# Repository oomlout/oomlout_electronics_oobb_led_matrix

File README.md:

# oomlout_oobb_led_matrix
## Description
an electronics project that is an led matrix in the oobb shape, current version is 3 x 10 oobb with 6 columns and 15 rows of leds, it uses the aip1640 16 x 8 driver chip/

## Images

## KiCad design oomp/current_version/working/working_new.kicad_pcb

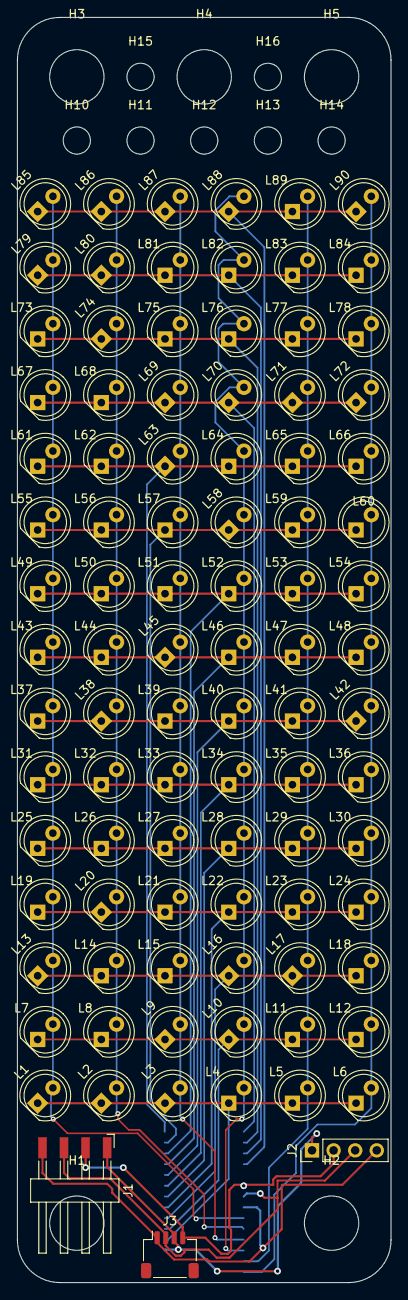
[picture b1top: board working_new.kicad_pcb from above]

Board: 2 copper layers, 44.0 x 149.0 mm, 106 parts (1 on the bottom side), 25 nets.

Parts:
H1, H2, H3, H4, H5: mhm6_fbea65_electronic_mounting_hole_m6
H10, H11, H12, H13, H14, H15, H16: mhm3_872f01_electronic_mounting_hole_m3
J1: hi14psmra_70c043_electronic_header_2d54_mm_4_pin_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; hi14psmra_70c043_electronic_header_2d54_mm_4_pin_surface_mo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
J2: hi14p_abf4a4_electronic_header_2d54_mm_4_pin
J3: h4psmra_adfe77_electronic_header_1_mm_jst_sh_4_pi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; h4psmra_adfe77_electronic_header_1_mm_jst_sh_4_pin_surface_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
L1, L2, L3, L4, L5, L6, L7, L8, L9, L10, L11, L12, L13, L14, L15, L16, L17, L18, L19, L20, L21, L22, L23, L24, L25, L26, L27, L28, L29, L30, L31, L32, L33, L34, L35, L36, L37, L38, L39, L40, L41, L42, L43, L44, L45, L46, L47, L48, L49, L50, L51, L52, L53, L54, L55, L56, L57, L58, L59, L60, L61, L62, L63, L64, L65, L66, L67, L68, L69, L70, L71, L72, L73, L74, L75, L76, L77, L78, L79, L80, L81, L82, L83, L84, L85, L86, L87, L88, L89, L90: l5_electronic_led_5_mm; l5_7297cd_electronic_led_5_mm
U1: iaip1640_electronic_ic_soic_28_wide_led_matrix_dr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; iaip1640_fe0f02_electronic_ic_soic_28_wide_led_matrix_drive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

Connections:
+5V: J1.1, J2.1, J3.3, U1.17 (___vdd)
/clk: J1.4, J2.4, J3.1, U1.8 (___sclk)
/col_1: L1.1 (K), L2.1 (K), L3.1 (K), L4.1 (K), L5.1 (K), L6.1 (K), U1.18 (___grid1)
/col_2: L7.1 (K), L8.1 (K), L9.1 (K), L10.1 (K), L11.1 (K), L12.1 (K), U1.19 (___grid2)
/col_3: L13.1 (K), L14.1 (K), L15.1 (K), L16.1 (K), L17.1 (K), L18.1 (K), U1.20 (___grid3)
/col_4: L19.1 (K), L20.1 (K), L21.1 (K), L22.1 (K), L23.1 (K), L24.1 (K), U1.21 (___grid4)
/col_5: L25.1 (K), L26.1 (K), L27.1 (K), L28.1 (K), L29.1 (K), L30.1 (K), U1.22 (___grid5)
/col_6: L31.1 (K), L32.1 (K), L33.1 (K), L34.1 (K), L35.1 (K), L36.1 (K), U1.23 (___grid6)
/col_7: L37.1 (K), L38.1 (K), L39.1 (K), L40.1 (K), L41.1 (K), L42.1 (K), U1.24 (___grid7)
/col_8: L43.1 (K), L44.1 (K), L45.1 (K), L46.1 (K), L47.1 (K), L48.1 (K), U1.25 (___grid8)
/col_9: L49.1 (K), L50.1 (K), L51.1 (K), L52.1 (K), L53.1 (K), L54.1 (K), U1.26 (___grid9)
/col_10: L55.1 (K), L56.1 (K), L57.1 (K), L58.1 (K), L59.1 (K), L60.1 (K), U1.27 (___grid10)
/col_11: L61.1 (K), L62.1 (K), L63.1 (K), L64.1 (K), L65.1 (K), L66.1 (K), U1.28 (___grid11)
/col_12: L67.1 (K), L68.1 (K), L69.1 (K), L70.1 (K), L71.1 (K), L72.1 (K), U1.1 (___grid12)
/col_13: L73.1 (K), L74.1 (K), L75.1 (K), L76.1 (K), L77.1 (K), L78.1 (K), U1.2 (___grid13)
/col_14: L79.1 (K), L80.1 (K), L81.1 (K), L82.1 (K), L83.1 (K), L84.1 (K), U1.3 (___grid14)
/col_15: L85.1 (K), L86.1 (K), L87.1 (K), L88.1 (K), L89.1 (K), L90.1 (K), U1.4 (___grid15)
/data: J1.3, J2.3, J3.2, U1.7 (___din)
/row_1: L1.2 (A), L7.2 (A), L13.2 (A), L19.2 (A), L25.2 (A), L31.2 (A), L37.2 (A), L43.2 (A), L49.2 (A), L55.2 (A), L61.2 (A), L67.2 (A), L73.2 (A), L79.2 (A), L85.2 (A), U1.9 (___seg1)
/row_2: L2.2 (A), L8.2 (A), L14.2 (A), L20.2 (A), L26.2 (A), L32.2 (A), L38.2 (A), L44.2 (A), L50.2 (A), L56.2 (A), L62.2 (A), L68.2 (A), L74.2 (A), L80.2 (A), L86.2 (A), U1.10 (___seg2)
/row_3: L3.2 (A), L9.2 (A), L15.2 (A), L21.2 (A), L27.2 (A), L33.2 (A), L39.2 (A), L45.2 (A), L51.2 (A), L57.2 (A), L63.2 (A), L69.2 (A), L75.2 (A), L81.2 (A), L87.2 (A), U1.11 (___seg3)
/row_4: L4.2 (A), L10.2 (A), L16.2 (A), L22.2 (A), L28.2 (A), L34.2 (A), L40.2 (A), L46.2 (A), L52.2 (A), L58.2 (A), L64.2 (A), L70.2 (A), L76.2 (A), L82.2 (A), L88.2 (A), U1.12 (___seg4)
/row_5: L5.2 (A), L11.2 (A), L17.2 (A), L23.2 (A), L29.2 (A), L35.2 (A), L41.2 (A), L47.2 (A), L53.2 (A), L59.2 (A), L65.2 (A), L71.2 (A), L77.2 (A), L83.2 (A), L89.2 (A), U1.13 (___seg5)
/row_6: L6.2 (A), L12.2 (A), L18.2 (A), L24.2 (A), L30.2 (A), L36.2 (A), L42.2 (A), L48.2 (A), L54.2 (A), L60.2 (A), L66.2 (A), L72.2 (A), L78.2 (A), L84.2 (A), L90.2 (A), U1.14 (___seg6)
GND: J1.2, J2.2, J3.4, U1.6 (___vss)

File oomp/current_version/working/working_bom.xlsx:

|  | KiBot Bill of Materials
 |  | Schematic: | working | Component Groups: | 7
 |  | Variant: | default | Component Count: | 106 (3 SMD/ 91 THT)
 |  | Revision: |  | Fitted Components: | 106 (3 SMD/ 91 THT)
 |  | Date: | 2023-08-02_18-16-06 | Number of PCBs: | 1
 |  | KiCad Version: | 7.0.6-7.0.6~ubuntu22.04.1 | Total Components: | 106
Row | Description | Part | Part Lib | References | Value | Footprint | Footprint Lib | Quantity Per PCB | Build Quantity | Status | Datasheet | Sheetpath | Source BoM | Footprint X | Footprint Y | Footprint Rot | Footprint Side | Footprint Type | Footprint Populate | Footprint X-Size | Footprint Y-Size
1 | Mounting Hole without connection | mhm3_872f01_electronic_mounting_hole_m3 | oomlout_oomp_kicad_symbols | H10 H11 H12 H13 H14 H15 H16 | mhm3_872f01_electronic_mounting_hole_m3 | mhm3_872f01_electronic_mounting_hole_m3 | oomlout_oomp_footprints | 7 | 7 |  | https://github.com/oomlout/oomlout_oomp_v3/parts/electronic_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 | / | working(7) | -15.0000 | 60.0000 | 0.0000 | top | SMD | yes | 3.2000 | 3.2000
2 | Mounting Hole without connection | mhm6_fbea65_electronic_mounting_hole_m6 | oomlout_oomp_kicad_symbols | H1 H2 H3 H4 H5 | mhm6_fbea65_electronic_mounting_hole_m6 | mhm6_fbea65_electronic_mounting_hole_m6 | oomlout_oomp_footprints | 5 | 5 |  | https://github.com/oomlout/oomlout_oomp_v3/parts/electronic_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 | / | working(5) | -15.0000 | -67.5000 | 0.0000 | top | SMD | yes | 6.4000 | 6.4000
3 | Generic connector, single row, 01x04, script generated (kicad-library-utils/sch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 | h4psmra_adfe77_electronic_header_1_mm_jst_sh_4_pin_surface_mount_right_angle | oomlout_oomp_kicad_symbols | J3 | h4psmra_adfe77_electronic_header_1_mm_jst_sh_4_pin_surface_mount_right_angle | h4psmra_adfe77_electronic_header_1_mm_jst_sh_4_pin_surface_mount_right_angle | oomlout_oomp_footprints | 1 | 1 |  | https://github.com/oomlout/oomlout_oomp_v3/parts/electronic_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 | / | working(1) | -4.0400 | -71.2150 | 0.0000 | top | SMD | yes | 6.8000 | 5.5500
4 | Generic connector, single row, 01x04, script generated (kicad-library-utils/sch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 | hi14p_abf4a4_electronic_header_2d54_mm_4_pin | oomlout_oomp_kicad_symbols | J2 | hi14p_abf4a4_electronic_header_2d54_mm_4_pin | hi14p_abf4a4_electronic_header_2d54_mm_4_pin | oomlout_oomp_footprints | 1 | 1 |  | https://github.com/oomlout/oomlout_oomp_v3/parts/electronic_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 | / | working(1) | 12.7000 | -58.9280 | 90.0000 | top | THT | yes | 1.7000 | 9.3200
5 | Generic connector, single row, 01x04, script generated (kicad-library-utils/sch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 | hi14psmra_70c043_electronic_header_2d54_mm_4_pin_surface_mount_right_angle | oomlout_oomp_kicad_symbols | J1 | hi14psmra_70c043_electronic_header_2d54_mm_4_pin_surface_mount_right_angle | hi14psmra_70c043_electronic_header_2d54_mm_4_pin_surface_mount_right_angle | oomlout_oomp_footprints | 1 | 1 |  | https://github.com/oomlout/oomlout_oomp_v3/parts/electronic_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 | / | working(1) | -15.2400 | -64.1350 | 270.0000 | top | SMD | yes | 13.6700 | 8.6200
6 | Light emitting diode | l5_7297cd_electronic_led_5_mm | oomlout_oomp_kicad_symbols | L1 L2 L3 L4 L5 L6 L7 L8 L9 L10 L11 L12 L13 L14 L15 L16 L17 L18 L19 L20 L21 L22 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 | l5_electronic_led_5_mm | l5_7297cd_electronic_led_5_mm | oomlout_oomp_footprints | 90 | 90 |  | https://github.com/oomlout/oomlout_oomp_v3/parts/electronic_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 | / | working(90) | -19.6160 | -53.3660 | 45.0000 | top | THT | yes | 4.3400 | 1.8000
7 | Generic connector, single row, 01x28, script generated (kicad-library-utils/sch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 | iaip1640_fe0f02_electronic_ic_soic_28_wide_led_matrix_driver_16_x_8_wuxi_i_core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 | oomlout_oomp_kicad_symbols | U1 | iaip1640_electronic_ic_soic_28_wide_led_matrix_driver_16_x_8_wuxi_i_core_electr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 | iaip1640_fe0f02_electronic_ic_soic_28_wide_led_matrix_driver_16_x_8_wuxi_i_core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 | oomlout_oomp_footprints | 1 | 1 |  | https://github.com/oomlout/oomlout_oomp_v3/parts/electronic_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 | / | working(1) | 0.0000 | -65.0000 | 180.0000 | bottom | SMD | yes | 11.3500 | 17.1100

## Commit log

2023-07-20 update to corel draw file
2023-07-21 test new readme
2023-07-21 reademe fixup
2023-07-21 test readme
2023-07-21 readme updated
2023-07-21 test
2023-07-21 test readme and generations
2023-07-21 fixed images?
2023-07-21 fixed slashes
2023-07-22 swapped location of main file
2023-07-23 removed copy
2023-07-23 took away new pcb
2023-07-23 moved from current to active
2023-07-23 moved back to current
2023-08-02 change folder name
2023-08-02 added kibot config
2023-08-02 simplified kibot config
2023-08-02 first kibot test
2023-08-02 changed kibot yaml
2023-08-02 removed documentation
2023-08-02 fresh
2023-08-02 removed gens
2023-08-02 new try of kibot
2023-08-02 gen run
2023-08-02 trial two
2023-09-03 tiny change
